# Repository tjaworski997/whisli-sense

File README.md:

<div align="right"><a href="README.pl.md">Polski</a> · <b>English</b></div>

# whisli sense

A presence sensor for the home that also sees a person sitting still. Its mmWave radar picks up even
breathing, and next to it the sensor measures temperature, humidity and light. It runs on its own
over Wi-Fi, has its own panel in the browser and, if you want, announces itself to Home Assistant.

## Concept

- **Presence, not motion.** A regular PIR sensor turns the light off while you read or watch a film.
  The mmWave radar sees the tiny movements of breathing, so presence lasts as long as someone is there.
- **Everything local.** No cloud, no accounts, no internet. Every sensor has its own panel and API;
  Home Assistant over MQTT is an extra, not a requirement.
- **No hub.** Sensors find each other on the network (mDNS). The panel of any of them shows all of
  them – none is the "main" one, so one failing does not take the others down.
- **Fitted to the room.** A 1.5-minute calibration measures the empty room's noise and a sitting
  person's breathing, then sets the thresholds of every radar gate by itself.
- **Everything through the API.** Every panel feature is available through a simple JSON API, so the
  sensor fits into any system.
- **Simple.** Small, readable code: C++ firmware (Arduino on ESP-IDF) and a React panel built into the
  firmware – one file to flash.

## Hardware

| Part | Model | Role |
|---|---|---|
| Microcontroller | Waveshare **ESP32-C3-Zero** (RISC-V 160 MHz, 4 MB flash, 2.4 GHz Wi-Fi, USB-C, WS2812 RGB LED) | firmware, Wi-Fi, web panel, status LED |
| Radar | Waveshare **HMMD mmWave** (S3KM1110 chip, 24 GHz) | presence and distance, energy in 16 gates of 70 cm (up to 11.2 m) |
| Temperature and humidity | Sensirion **SHT30** (I²C) | room climate |
| Light | ROHM **BH1750** (I²C) | illuminance in lux |

Powered over USB-C (5 V); the modules run from the board's 3.3 V. Wiring is in the
[technical documentation](#hardware-and-wiring).

A ceiling enclosure and a carrier PCB (modules soldered flat, 5–36 V input) are in
[`hardware/`](hardware/README.md) – status and next steps in Polish.

<p align="center">
  <br>
  <sub>The breadboard prototype – from the left: ESP32-C3-Zero, HMMD mmWave radar, SHT3x, BH1750.</sub>
</p>

## Features

### Start – live presence

A top view of the radar with a wave "searching" for the person, the distance, a 2-minute presence
timeline, temperature, humidity and light with charts, plus the minimum and maximum over 24 h, 7 and
30 days. Optional beeping like a parking sensor – the closer the person, the faster.

### Radar – range and sensitivity

Detection range (from – to) and the presence timeout. For each of the 16 gates you see live motion
against its threshold; drag the line to change the threshold. Everything saves by itself.

### Calibration

The wizard guides you with text, sound and a radar animation: you leave for a moment (noise), come
back and sit down (breathing). The sensor times the steps and saves the thresholds; the previous ones
are one click away.

### Nearby – all sensors on the network

A graph or a table of all sensors: presence, climate, Wi-Fi strength, IP and MAC. The panel connects
to each sensor directly. The screenshots show two real sensors and ten from the panel's demo mode.

### Status LED

Blinking by distance, lit while someone is there, problems only, or off. Plus colour, brightness and
staying dark at night (light sensor).

### Diagnostics and event log

Chip, memory, Wi-Fi, radar, sensors and MQTT status, the latest events and a one-click report
download. A separate page has the full event log with filters.

### More

- **Home Assistant (MQTT Discovery)** – the sensor creates its own device with entities: occupancy,
  distance, temperature, humidity, illuminance, Wi-Fi signal.
- **First setup without a cable** – without Wi-Fi the sensor opens its own access point with the setup panel.
- **Panel password** – sign-in with "remember me for 30 days", HTTP Basic for scripts, reset with the BOOT button.
- **Updates over Wi-Fi** – new firmware from the panel or with a single `curl` command.
- **Two languages, two themes** – Polish and English, light and dark.

## Installation

Ready firmware is in [Releases](https://github.com/tjaworski997/whisli-sense/releases/latest):

- **first time, over USB** – `whisli-sense-<version>-full.bin` at address `0x0`, e.g. from the browser with
  [esptool-js](https://espressif.github.io/esptool-js/) (Chrome or Edge) or
  `esptool.py --chip esp32c3 write_flash 0x0 whisli-sense-<version>-full.bin`,
- **updates, over Wi-Fi** – `whisli-sense-<version>.bin` in the panel (System → Settings → Firmware).

## Quick start

1. Power it up. A new sensor opens the Wi-Fi network **Whisli-Sense-XXXX** (password `whisli_gogo`).
2. Join it and open `http://192.168.4.1/`. Panel password: `whisli_gogo`.
3. **System → Network**: pick your Wi-Fi and connect. The sensor will be at `http://whisli-<name>.local/`.
4. **System → Settings**: give it a name (e.g. "Living room") and change the password.
5. **Radar → Calibration**: fit the sensitivity to the room (about 1.5 minutes).

Holding the BOOT button for 10 s restores the default panel password.

### LED

Dark by default while all is well. Problems: blue blink every 2 s – no Wi-Fi, red every 3 s – a
sensor fault. Fast white – BOOT is held. Other modes: **System → Status LED**.

---

# Technical documentation

## Hardware and wiring

All modules are powered from the board's 3V3 and GND.

| Signal | GPIO |
|---|---|
| I²C SDA / SCL (SHT30 0x44, BH1750 0x23) | 4 / 5 |
| Radar TX → ESP RX | 6 |
| ESP TX → Radar RX | 7 |
| Radar OT2 (presence) | 3 |
| WS2812 LED (on the board) | 10 |
| BOOT (on the board) | 9 |

## Building

Needs [PlatformIO](https://platformio.org/) and Node.js.

```
cd ui && npm install && cd ..
pio run                      # builds the panel (ui/) and the firmware
pio run -t upload            # over USB (always USB when the partition table changes)
WHISLI_SENSE_PASSWORD=<password> pio run -e ota -t upload --upload-port whisli-salon.local
```

`scripts/prebuild.py` builds the panel, gzips it into `src/generated/ui.h` and stamps the version
`0.001.YYYYMMDDHHMM`, shared by firmware and panel. `WHISLI_SENSE_SKIP_UI=1 pio run` skips the panel
(faster firmware-only builds).

Panel against a live sensor, with live reload: `cd ui && SENSE_DEVICE_URL=http://<sensor ip> npm run dev`.
In this mode `http://localhost:5173/?demo=10#/sensors` adds 10 made-up sensors.

GitHub release: `scripts/release.sh` (builds without the local Wi-Fi and publishes both files).

To have a board join Wi-Fi straight away, copy `src/local_defaults.example.h` to
`src/local_defaults.h` and fill in the network. The file is not committed.

## Minimum and maximum

The sensor keeps the lowest and highest temperature, humidity and light over the last 24 h, 7 and 30
days (`extremes.day` / `week` / `month` in the state). It stores 24 hourly and 30 daily buckets in NVS
(`sense-extremes`), saved every 10 minutes and before every restart from the panel or API (also after
OTA) – a sudden power cut loses at most 10 minutes. Time is taken from the clock (SNTP,
`pool.ntp.org`), so the time the sensor was off counts too; without internet only uptime counts. A
day is 24 hours of running since the first save, not a calendar day.

## API

Everything the panel does is available through the API under `/api/v1`. POST takes form fields,
answers are JSON, errors `{"error":"<code>"}`. Access: the panel session or HTTP Basic
(`curl -u whisli:<password> …`).

| Method and path | What it does |
|---|---|
| `GET /api/v1/state` | full state: presence, distance, climate, min/max of temperature, humidity and light (`extremes`), radar (thresholds, energy), calibration, problems, Wi-Fi (`rssi`, `ip`, `mac`), `heap`, clock (`clock`, Unix time from NTP or `null`) |
| `ws://…/api/v1/ws` | the same every second and at once when presence changes |
| `ws://…/api/v1/live` | short summary for the sensors overview (with `rssi`, `ip`, `mac`), every 10 s; **no sign-in** |
| `GET /api/v1/peers` | this sensor and the others found on the network (mDNS `_whisli-sense._tcp`) |
| `POST /api/v1/device` | `name` (1–32 characters); the hostname is made from it |
| `POST /api/v1/radar` | `minGate`, `maxGate` (0–15, gate = 70 cm), `delay` (0–600 s), `p0`…`p15` (presence threshold: hold = p, trigger = 1.5 × p), `t0`…`t15` / `h0`…`h15` (raw thresholds, 0–65535), `factory=1` |
| `POST /api/v1/calibration` | `action`: `start` (optional `leave`, `empty`, `back`, `still` in s, `margin` in %), `seated`, `cancel`, `undo` |
| `GET/POST /api/v1/wifi` | network status / `ssid`, `password` – connect |
| `POST /api/v1/wifi/forget` | forget the network (opens the access point) |
| `POST`, `GET /api/v1/wifi/scan` | scan / results |
| `POST /api/v1/wifi/ap` | `password` – access point password |
| `GET/POST /api/v1/mqtt` | MQTT settings: `enabled`, `host`, `port`, `user`, `password`, `clearPassword`, `baseTopic`, `discovery`, `discoveryPrefix` |
| `GET/POST /api/v1/led` | LED: `mode` (`off`, `status`, `presence`, `distance` – blinks faster the closer the person), `color` (`blue`, `green`, `white`, `purple`, `amber`), `brightness` (1–100 %), `alerts`, `darkOff` (stay dark in the dark) |
| `GET /api/v1/logs` | event log (RAM, up to 120 entries): `after`, `before` (entry id), `limit`, `level`, `category` |
| `GET /api/v1/system` | version, memory, uptime, reset reason |
| `GET /api/v1/diagnostics` | sensors, radar, chip (memory, flash, main loop), Wi-Fi, MQTT |
| `POST /api/v1/system/restart` | restart |
| `POST /api/v1/firmware` | new firmware as the raw body (`application/octet-stream`) |
| `GET /api/v1/auth`, `POST /api/v1/auth/login`, `…/logout`, `…/password` | `GET` without sign-in: signed in or not, plus the sensor's name, hostname and IP (for the login screen); sign-in (`password`, `remember=1` – a 30-day session that survives restarts), password change (`current`, `password`) |

## Radar

Report mode: about 10 frames a second with presence, distance and the energy in 16 gates of 70 cm.
Each gate has two thresholds in the radar: **trigger** (motion) and **hold** (micro-motion, breathing).
Presence starts above the trigger and lasts while the energy stays above hold, plus the timeout. The
panel shows one "presence threshold" (hold) and keeps the trigger 1.5× higher. The settings live in
the radar; when it stops sending (e.g. after a power cut), the firmware sets report mode again and
reads the settings back.

Calibration: noise = maximum energy in the empty room; "person" = 20th percentile of the per-second
maxima while sitting. Gate with the person (≥ 1.3 × noise): hold = noise × (person/noise)^0.4 (at least
noise × 1.15), trigger = hold × 1.5. Other gates: hold = noise × (1 + margin), trigger = hold × (1 + margin).

## MQTT (Home Assistant)

One device in HA (`whisli_sense_<id>`, `<id>` = last MAC bytes) with entities: Occupancy, Distance,
Temperature, Humidity, Illuminance, Wi-Fi signal (in English whatever the panel language; rename
them in HA if you like).

| Topic | Payload |
|---|---|
| `whisli-sense/<id>/status` | `online` / `offline` (retained, last will) |
| `whisli-sense/<id>/state` | `{"occupancy":"ON","distance":2.05,"temperature":24.9,"humidity":47,"lux":62,"rssi":-52}` |

Presence changes are sent at once; distance, climate and light at most every 2 s and only on change;
otherwise the state goes out every minute.

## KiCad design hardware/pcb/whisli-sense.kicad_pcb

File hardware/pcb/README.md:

# Płytka whisli sense

Okrągła płytka nośna Ø72 mm do obudowy sufitowej (`../enclosure`). Gotowe moduły lutuje się
**na płasko, bez goldpinów**. Z płytki zamawia się sam laminat, bez montażu.

## Pliki

| Plik | Co to jest |
|---|---|
| `whisli_sense_pcb.py` | źródło płytki: skrypt buduje całość od zera, wymiary i połączenia na górze pliku |
| `whisli-sense.kicad_pcb`, `.kicad_pro` | wynik skryptu: do podglądu w KiCadzie i do eksportu Gerberów |

Płytka zmienia się **tylko w skrypcie**. Ręczne poprawki w KiCadzie znikną przy następnym
uruchomieniu skryptu. Uruchomienie (KiCad 10):

```sh
/Applications/KiCad/KiCad.app/Contents/Frameworks/Python.framework/Versions/Current/bin/python3 \
    hardware/pcb/whisli_sense_pcb.py
```

Skrypt na końcu wywołuje `kicad-cli pcb drc --refill-zones`, który wylewa miedź i sprawdza płytkę.
Raport trafia do `drc.rpt`. Musi pokazywać 0 naruszeń i 0 niepołączonych padów.

## Układ (widok od strony pomieszczenia, +Y to tył, −Y to przód z logo)

**Przód (F, do pomieszczenia):**

| Ozn. | Moduł | Gdzie |
|---|---|---|
| U2 | radar HMMD 20 × 20 | środek, anteny w stronę pokrywy |
| U5 | BH1750 GY-302 | czujnik pod okienkiem światła (0; 18,5) |
| U4 | SCD41 (opcja) | komora czujników, z lewej |
| U3 | SHT3x | komora czujników, z prawej, czujnik w stronę kratki |

**Tył (B, do sufitu):**

| Ozn. | Moduł | Gdzie |
|---|---|---|
| U1 | ESP32-C3-Zero | półotwory przylutowane do padów, antena przy krawędzi, pod nią brak miedzi |
| U6 | Pololu D36V6F5 | przetwornica 5,2–50 V → 5 V |
| J1 | pady VIN / GND | przewody zasilania z otworu w podstawie |

**Pozostałe elementy:**

- Komora czujników ma ramkę drukowaną osobno i przyklejoną według obrysu na sitodruku.
- Szczelina pod komorą przerywa przepływ ciepła od ESP i przetwornicy.
- 3 otwory Ø2,8 na słupki M2,5 (r = 30 mm).
- Napis od strony sufitu: „whis.li sense” w Helvetica Neue (jak na pokrywie), wersja płytki
  (`VERSION` w skrypcie) oraz oznaczenie padów zasilania: + / − i 5–36 V.
  Przy nowej partii płytek podbij wersję. Font jest systemowy na macOS, więc Gerbery eksportuj na
  Macu, inaczej KiCad podstawi własny font.

## Połączenia

Piny ESP32 są te same co w `src/board.h`: I2C SDA 4 i SCL 5, radar RX 6 / TX 7 / OT2 3.

- Warstwa B to masa, warstwa F to +3V3.
- VIN i 5 V idą ścieżkami 0,6 mm, sygnały ścieżkami 0,3 mm.
- SHT3x (0x44), SCD41 (0x62) i BH1750 (0x23) siedzą na jednej magistrali I2C. Można wlutować
  SHT3x, SCD41 albo oba. Pull-upy są na modułach.

## Decyzje

- Moduły na płasko zamiast gotowych układów montowanych przez JLC: tanio, lutowanie lutownicą,
  firmware bez zmian.
- Bez diody między przetwornicą a USB: **nie podłączaj USB, gdy płytka jest zasilana z J1.**
  USB służy tylko do pierwszego wgrania, potem aktualizacje idą przez OTA.
- Bez zacisku śrubowego, który jest za wysoki na 6 mm od strony sufitu. Zamiast niego jest
  przewód ~15 cm przylutowany do J1 na biurku i połączony w puszce złączką WAGO 221. Każda żyła
  przechodzi najpierw przez otwór odciążający Ø2,2 pod padem (od sufitu na drugą stronę i z
  powrotem przez pad), więc szarpnięcie nie urwie lutu. Przewód silikonowy 0,25–0,5 mm².
- Przetwornica Pololu ma stałe wymiary i wejście do 50 V. Tanie MP1584 mają maks. ~28 V
  i różne rozmiary.

## Lutowanie na płasko

1. Z goldpinu zsuń plastikową listwę.
2. Wsuń piny przez moduł i płytkę, dociśnij moduł płasko i przylutuj z obu stron.
3. Utnij końcówki pinów.

C3-Zero przykłada się półotworami do padów i lutuje od boku.

## Do sprawdzenia przed zamówieniem

1. **Kolejność pinów kupionych modułów** z sitodrukiem płytki:
   - SHT3x: VIN, GND, SCL, SDA,
   - SCD41: VCC, GND, SCL, SDA,
   - BH1750: VCC, GND, SCL, SDA, ADDR.
2. Wymiary SHT3x i BH1750 wziąłem ze zdjęcia, a SCD41 to typowy moduł 13,4 × 21,6. Zmierzyć
   suwmiarką: chodzi o położenie rzędu pinów i czujnika.
3. Obudowa: zamiast drukowanej płytki montażowej wchodzi PCB 1,6 mm. Ramkę komory trzeba wydzielić
   jako osobną część, a w skrypcie obudowy przenieść `CHAMBER`, kratkę i makietę radaru (20 × 20).

## Zamówienie (JLCPCB)

Skrypt robi gotowy plik `fab/whisli-sense-<wersja>.zip` (Gerbery i wiercenia, poza gitem).
Wgraj go na https://cart.jlcpcb.com/quote. Parametry: 2 warstwy, 1,6 mm, HASL, dowolny kolor,
bez montażu (PCB Assembly wyłączone).

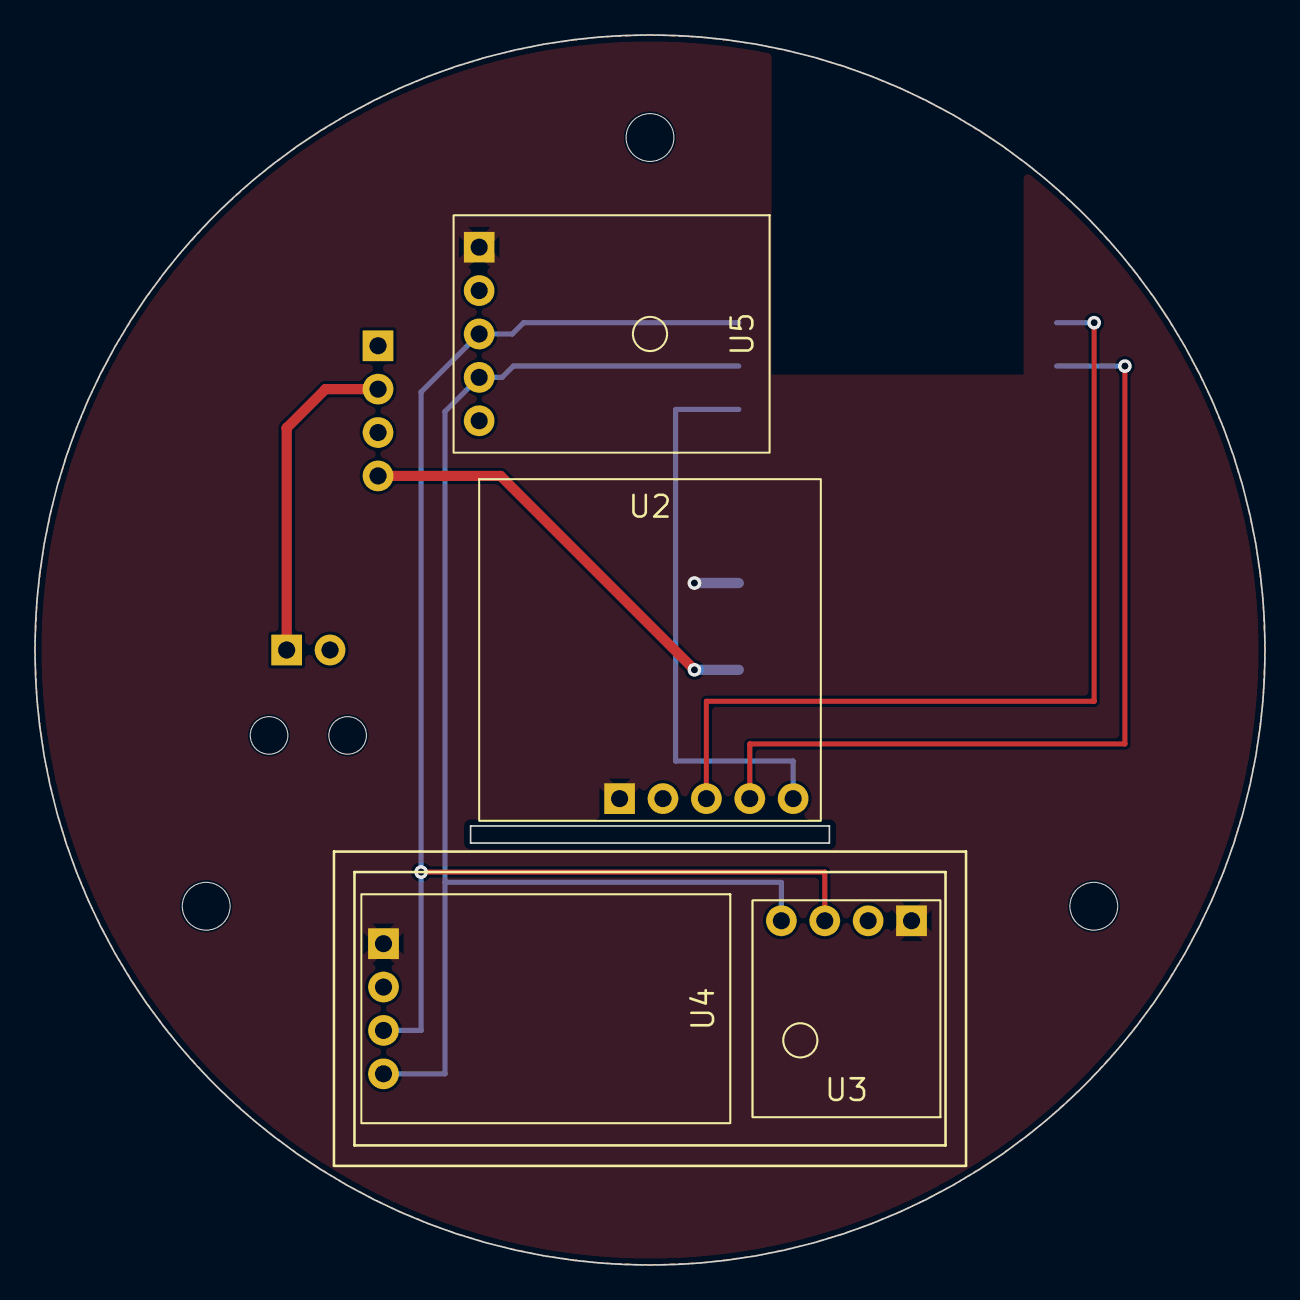
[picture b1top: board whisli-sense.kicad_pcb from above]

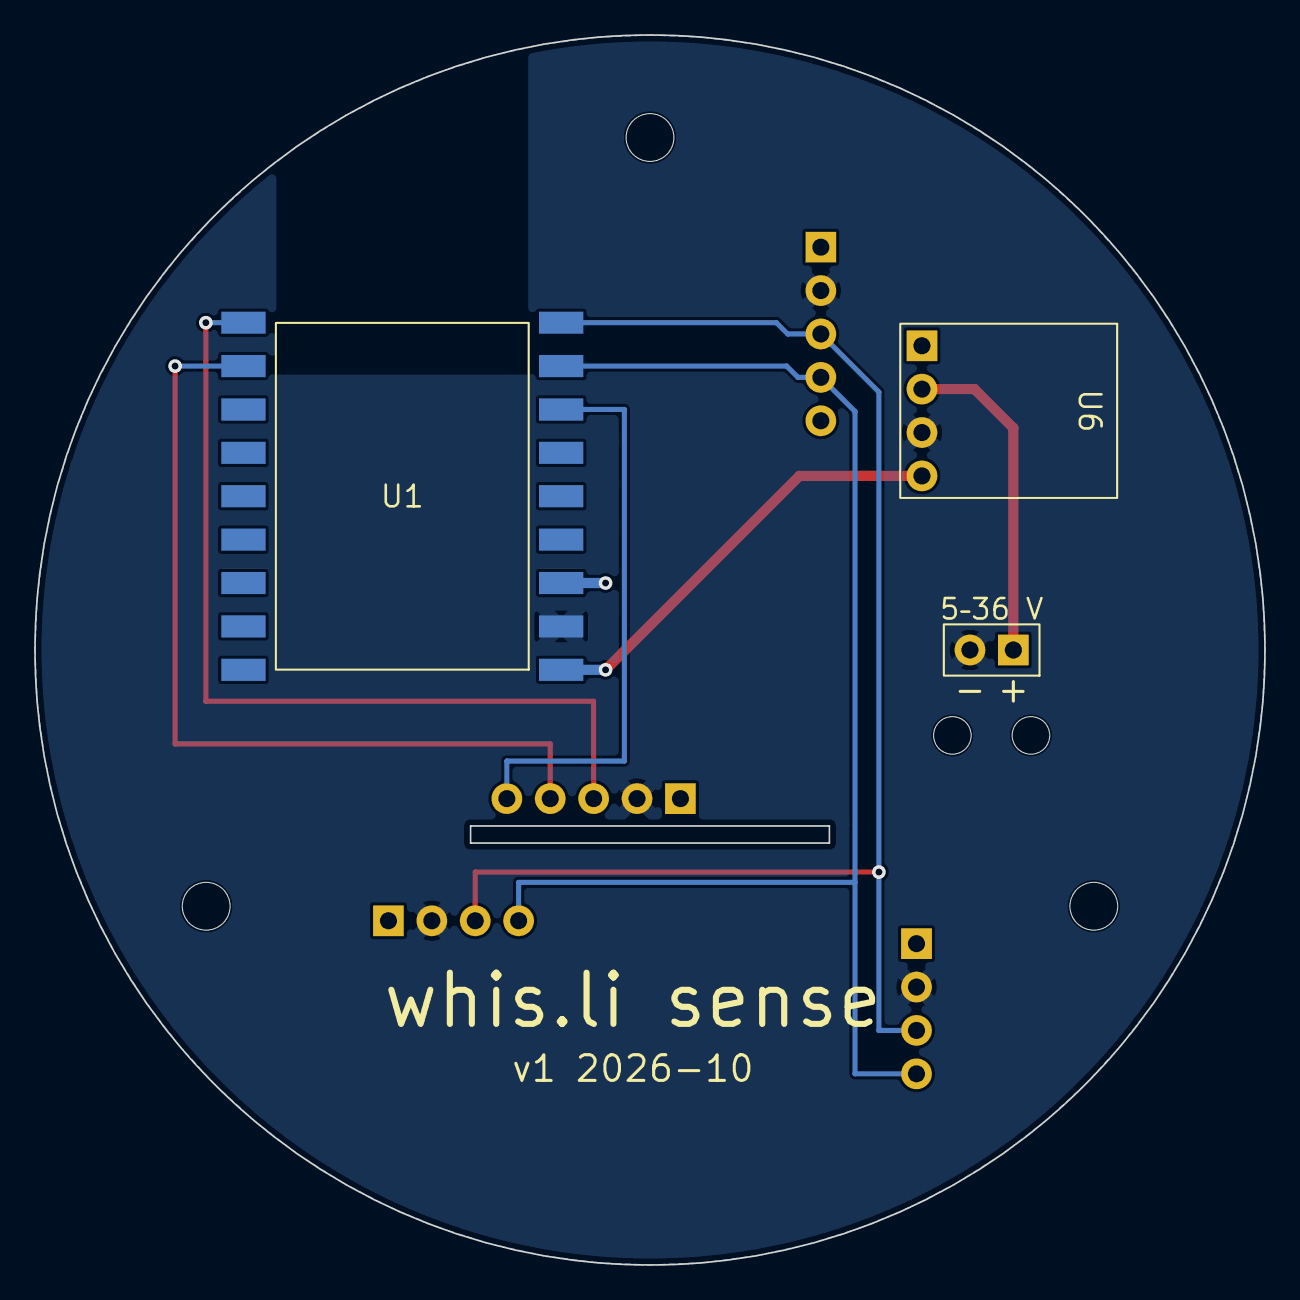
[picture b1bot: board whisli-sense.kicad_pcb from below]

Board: 2 copper layers, 72.0 x 72.0 mm, 12 parts (3 on the bottom side), 9 nets.

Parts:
H1, H2, H3, H4, H5: (no value)
J1: zasilanie 5-36 V
U1: ESP32-C3-Zero
U2: HMMD mmWave
U3: SHT3x
U4: SCD41
U5: BH1750 GY-302
U6: Pololu D36V6F5

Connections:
+3V3: U1.3V3, U2.3V3, U3.VIN, U4.VCC, U5.VCC
+5V: U1.5V, U6.VOUT
GND: J1.GND, U1.GND, U2.GND, U3.GND, U4.GND, U5.GND, U6.GND
RADAR_OUT: U1.IO3, U2.OT2
RADAR_RX: U1.IO6, U2.TX
RADAR_TX: U1.IO7, U2.RX
SCL: U1.IO5, U3.SCL, U4.SCL, U5.SCL
SDA: U1.IO4, U3.SDA, U4.SDA, U5.SDA
VIN: J1.VIN, U6.VIN

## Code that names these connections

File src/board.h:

#pragma once
// Wiring and fixed settings. Board: Waveshare ESP32-C3-Zero.
// Avoid GPIO 2, 8, 9 for new wiring (strapping pins) and 18/19 (USB).

namespace pins {
constexpr int I2C_SDA = 4;    // SHT30 + BH1750
constexpr int I2C_SCL = 5;
constexpr int RADAR_RX = 6;   // ESP RX <- radar TX
constexpr int RADAR_TX = 7;   // ESP TX -> radar RX
constexpr int RADAR_OUT = 3;  // radar OT2, high while someone is present
constexpr int LED = 10;       // on-board WS2812
constexpr int BOOT = 9;       // BOOT button; holding it 10 s resets the panel password
}  // namespace pins

// Panel password and access point password until the user changes them.
constexpr const char *DEFAULT_PASSWORD = "whisli_gogo";
